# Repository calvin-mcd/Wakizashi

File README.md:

# Wakizashi
 
Another collaboration with Falconloft4615. The wakizashi is a simple controller drop in PCB, with the aim to support BLE controller. This is a katana staggered layout with an adundance of options for the alpha cluster as well as the bottomrow.

## Layout

[Link](http://www.keyboard-layout-editor.com/#/gists/63cf34c3830b2de49229a321a906cf57)

## Pictures

## Todo

- [ ] order & test pcb
- [ ] create firmware
- [ ] create simple sandwhich case 

## Disclaimer

Please note that this project is a work in progress with no guarantees of a working outcome. No-one involved in this project is responsible for any usage issues that may arise. Order at your own risk. Support will not be provided but pull requests will be reviewed and possibly accepted.

## License

Shield: 

This work is licensed under a  
[Creative Commons Attribution-NonCommercial-ShareAlike 4.0 International License](http://creativecommons.org/licenses/by-nc-sa/4.0/).

## Credits

Any questions, contact Falconloft4615 & Calvin0563 on Discord.

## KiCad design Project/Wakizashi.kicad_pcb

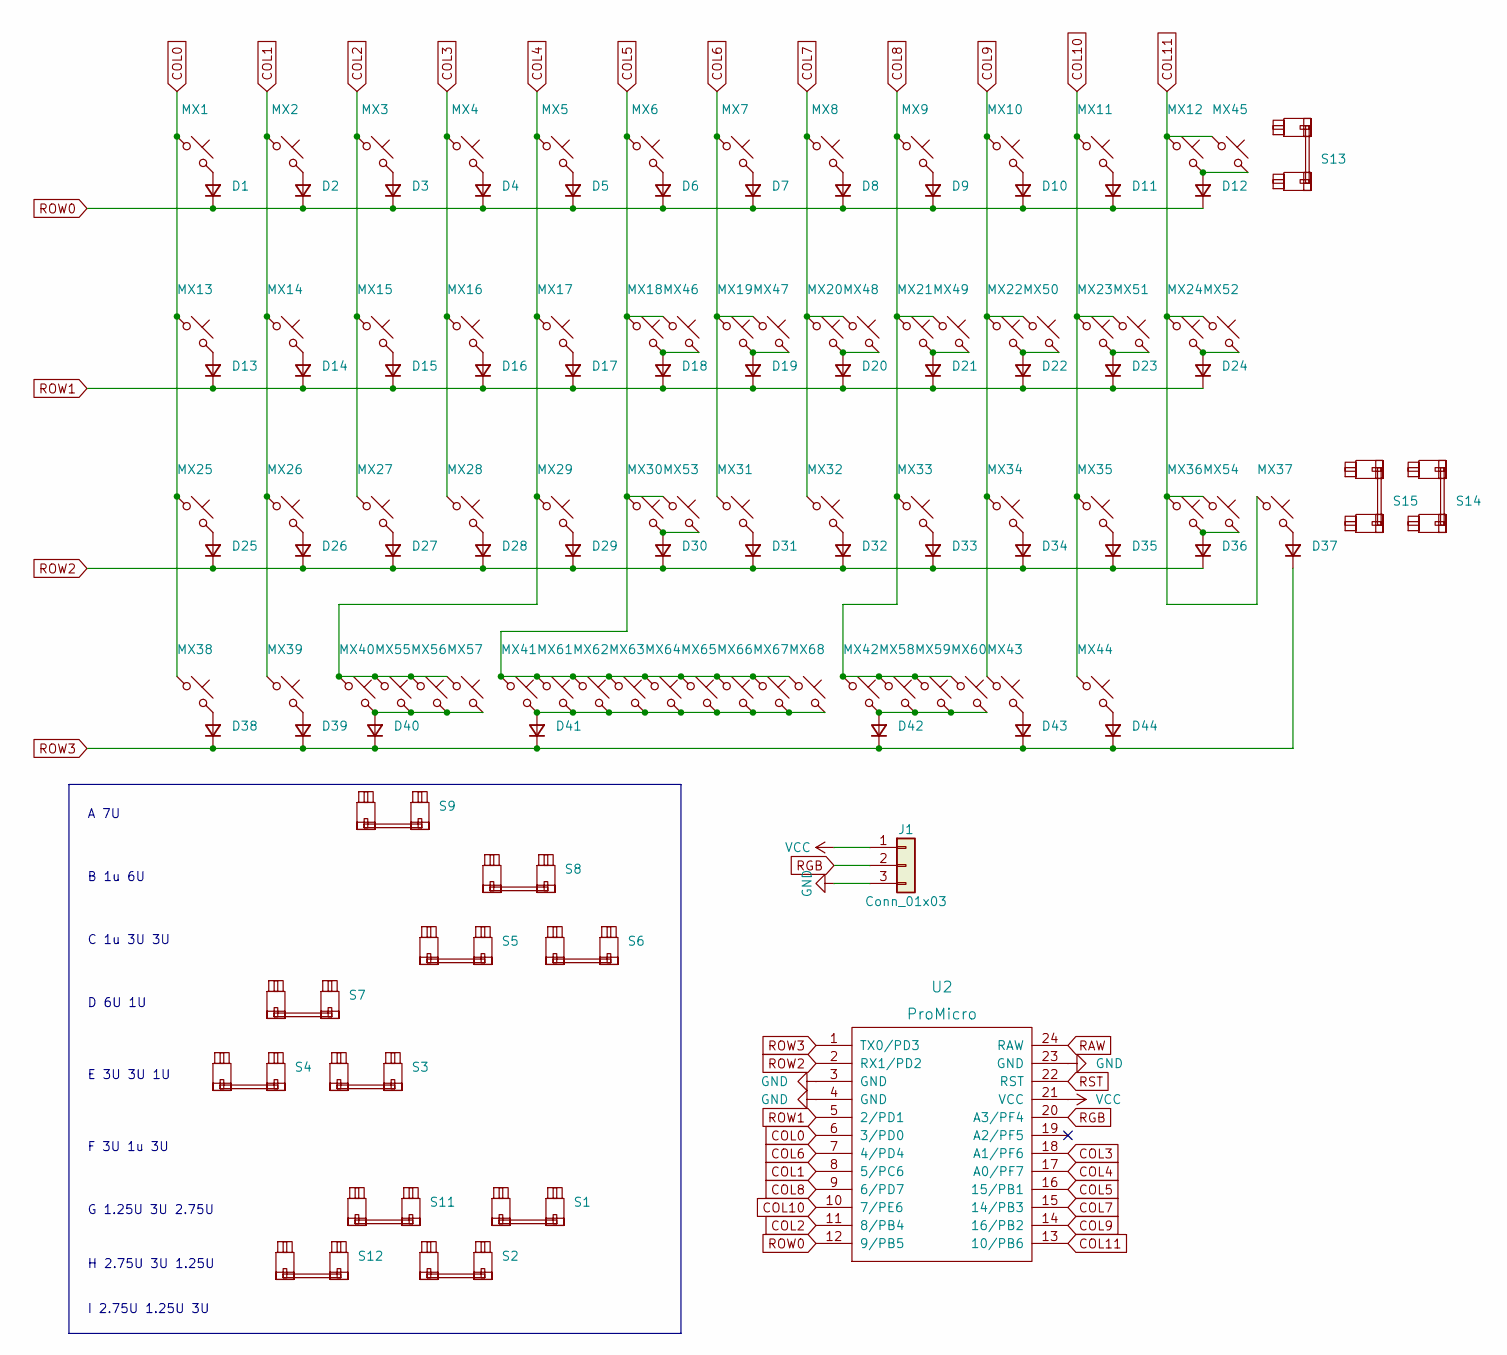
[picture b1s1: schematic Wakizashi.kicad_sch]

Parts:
D1, D2, D3, D4, D5, D6, D7, D8, D9, D10, D11, D12, D13, D14, D15, D16, D17, D18, D19, D20, D21, D22, D23, D24, D25, D26, D27, D28, D29, D30, D31, D32, D33, D34, D35, D36, D37, D38, D39, D40, D41, D42, D43, D44: D_Small; Diode-Hybrid-Back
J1: Conn_01x03; PinSocket_1x03_P2.54mm_Vertical
MX1, MX2, MX3, MX4, MX5, MX6, MX7, MX8, MX9, MX10, MX11, MX12, MX13, MX14, MX15, MX16, MX17, MX18, MX19, MX20, MX21, MX22, MX23, MX24, MX25, MX26, MX27, MX28, MX29, MX30, MX31, MX32, MX33, MX34, MX35, MX36, MX37, MX40, MX41, MX42, MX45, MX47, MX48, MX49, MX50, MX51, MX53, MX54, MX55, MX56, MX58, MX59, MX61, MX62, MX63, MX64, MX65, MX66, MX67: MX_SW_solder; SW_MX_1u
MX38, MX39, MX43, MX44, MX46, MX52: MX_SW_solder; SW_MX_1.5u
MX57, MX60, MX68: MX_SW_solder; SW_MX_1.25u
S1, S12: MX_stab; STAB_MX_2.75u
S2, S3, S4, S5, S6, S11: MX_stab; STAB_MX_3u
S7, S8: MX_stab; STAB_MX_6u
S9: MX_stab; STAB_MX_7u
S13, S14, S15: MX_stab; STAB_MX_2u
U2: ProMicro; ArduinoProMicro

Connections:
COL0: MX1.1, MX13.1, MX25.1, MX38.1, U2.6 (3/PD0)
COL1: MX2.1, MX14.1, MX26.1, MX39.1, U2.8 (5/PC6)
COL2: MX3.1, MX15.1, MX27.1, U2.11 (8/PB4)
COL3: MX4.1, MX16.1, MX28.1, U2.18 (A1/PF6)
COL4: MX5.1, MX17.1, MX29.1, MX40.1, MX55.1, MX56.1, MX57.1, U2.17 (A0/PF7)
COL5: MX6.1, MX18.1, MX30.1, MX41.1, MX46.1, MX53.1, MX61.1, MX62.1, MX63.1, MX64.1, MX65.1, MX66.1, MX67.1, MX68.1, U2.16 (15/PB1)
COL6: MX7.1, MX19.1, MX31.1, MX47.1, U2.7 (4/PD4)
COL7: MX8.1, MX20.1, MX32.1, MX48.1, U2.15 (14/PB3)
COL8: MX9.1, MX21.1, MX33.1, MX42.1, MX49.1, MX58.1, MX59.1, MX60.1, U2.9 (6/PD7)
COL9: MX10.1, MX22.1, MX34.1, MX43.1, MX50.1, U2.14 (16/PB2)
COL10: MX11.1, MX23.1, MX35.1, MX44.1, MX51.1, U2.10 (7/PE6)
COL11: MX12.1, MX24.1, MX36.1, MX37.1, MX45.1, MX52.1, MX54.1, U2.13 (10/PB6)
GND: J1.3, U2.3 (GND), U2.4 (GND), U2.23 (GND)
unnamed: D1.2 (A), MX1.2
unnamed: D2.2 (A), MX2.2
unnamed: D3.2 (A), MX3.2
unnamed: D4.2 (A), MX4.2
unnamed: D5.2 (A), MX5.2
unnamed: D6.2 (A), MX6.2
unnamed: D7.2 (A), MX7.2
unnamed: D8.2 (A), MX8.2
unnamed: D9.2 (A), MX9.2
unnamed: D10.2 (A), MX10.2
unnamed: D11.2 (A), MX11.2
unnamed: D12.2 (A), MX12.2, MX45.2
unnamed: D13.2 (A), MX13.2
unnamed: D14.2 (A), MX14.2
unnamed: D15.2 (A), MX15.2
unnamed: D16.2 (A), MX16.2
unnamed: D17.2 (A), MX17.2
unnamed: D18.2 (A), MX18.2, MX46.2
unnamed: D19.2 (A), MX19.2, MX47.2
unnamed: D20.2 (A), MX20.2, MX48.2
unnamed: D21.2 (A), MX21.2, MX49.2
unnamed: D22.2 (A), MX22.2, MX50.2
unnamed: D23.2 (A), MX23.2, MX51.2
unnamed: D24.2 (A), MX24.2, MX52.2
unnamed: D25.2 (A), MX25.2
unnamed: D26.2 (A), MX26.2
unnamed: D27.2 (A), MX27.2
unnamed: D28.2 (A), MX28.2
unnamed: D29.2 (A), MX29.2
unnamed: D30.2 (A), MX30.2, MX53.2
unnamed: D31.2 (A), MX31.2
unnamed: D32.2 (A), MX32.2
unnamed: D33.2 (A), MX33.2
unnamed: D34.2 (A), MX34.2
unnamed: D35.2 (A), MX35.2
unnamed: D36.2 (A), MX36.2, MX54.2
unnamed: D37.2 (A), MX37.2
unnamed: D38.2 (A), MX38.2
unnamed: D39.2 (A), MX39.2
unnamed: D40.2 (A), MX40.2, MX55.2, MX56.2, MX57.2
unnamed: D41.2 (A), MX41.2, MX61.2, MX62.2, MX63.2, MX64.2, MX65.2, MX66.2, MX67.2, MX68.2
unnamed: D42.2 (A), MX42.2, MX58.2, MX59.2, MX60.2
unnamed: D43.2 (A), MX43.2
unnamed: D44.2 (A), MX44.2
RAW: U2.24 (RAW)
RGB: J1.2, U2.20 (A3/PF4)
ROW0: D1.1 (K), D2.1 (K), D3.1 (K), D4.1 (K), D5.1 (K), D6.1 (K), D7.1 (K), D8.1 (K), D9.1 (K), D10.1 (K), D11.1 (K), D12.1 (K), U2.12 (9/PB5)
ROW1: D13.1 (K), D14.1 (K), D15.1 (K), D16.1 (K), D17.1 (K), D18.1 (K), D19.1 (K), D20.1 (K), D21.1 (K), D22.1 (K), D23.1 (K), D24.1 (K), U2.5 (2/PD1)
ROW2: D25.1 (K), D26.1 (K), D27.1 (K), D28.1 (K), D29.1 (K), D30.1 (K), D31.1 (K), D32.1 (K), D33.1 (K), D34.1 (K), D35.1 (K), D36.1 (K), U2.2 (RX1/PD2)
ROW3: D37.1 (K), D38.1 (K), D39.1 (K), D40.1 (K), D41.1 (K), D42.1 (K), D43.1 (K), D44.1 (K), U2.1 (TX0/PD3)
RST: U2.22 (RST)
VCC: J1.1, U2.21 (VCC)

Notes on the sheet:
G 1.25U 3U 2.75U
D 6U 1U
H 2.75U 3U 1.25U
C 1u 3U 3U
A 7U
B 1u 6U
E 3U 3U 1U
F 3U 1u 3U
I 2.75U 1.25U 3U

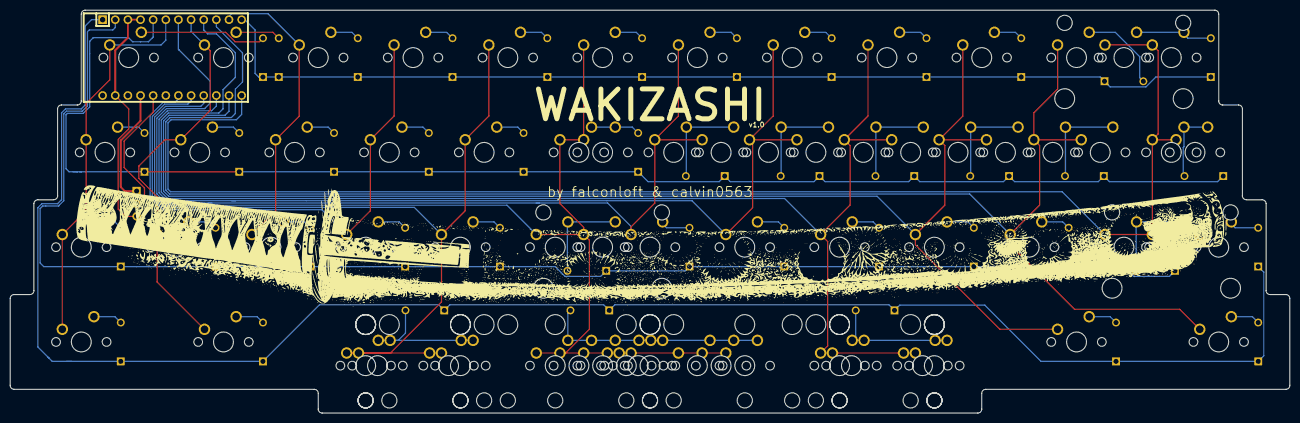
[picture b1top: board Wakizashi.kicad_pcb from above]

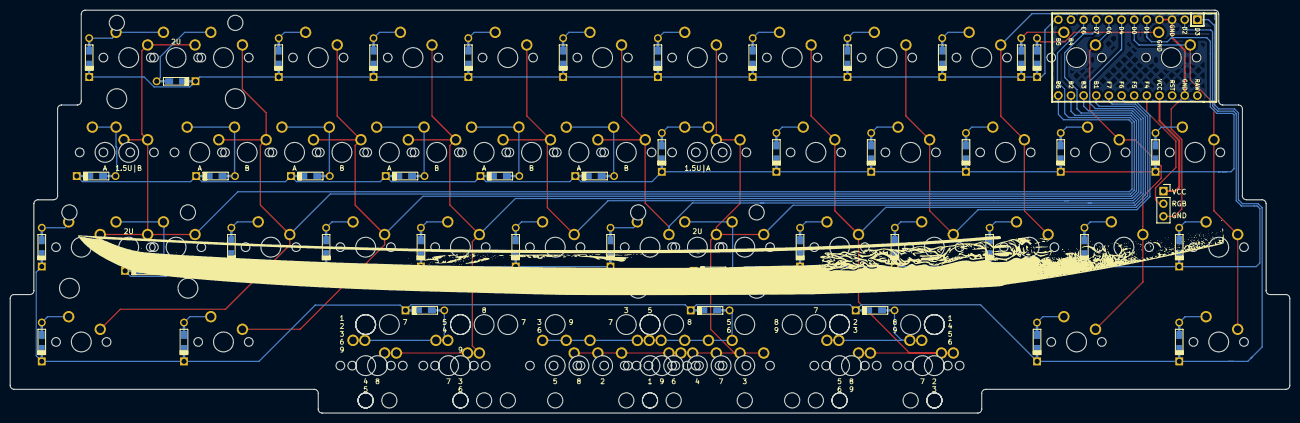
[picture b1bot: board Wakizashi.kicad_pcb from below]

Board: 2 copper layers, 257.2 x 81.0 mm, 128 parts (2 on the bottom side), 63 nets.

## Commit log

2023-09-11 cleaning up project
2023-09-12 update project
2023-09-15 backup
